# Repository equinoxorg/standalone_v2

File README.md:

#Standalone 2013 Designs

##Contents

* Hardware: The PCB designs for Pro and Home units
* Software: The source code of the embedded software
* Mechanical: The designs for the faceplate and physical casing
* Media: Any images or other media

##Hardware
This project includes hardware schematics and board layouts for Version 2 of the Standalone Battery Box (izuba.box) for e.quinox (www.e.quinox.org).

Cadsoft EAGLE v6 was the tool of choice when designing PCBs.

##Software

This project includes the ARM-based microcontroller software for Version 2 of the Standalone Battery Box (izuba.box) for e.quinox (www.e.quinox.org).

The project uses the Lite version of the Keil µVision IDE.

###Notes
Some code has been deliberately excluded as it would allow misuse of the payment system. If this is a problem please contact [info@e.quinox.org](mailto:info@e.quinox.org).

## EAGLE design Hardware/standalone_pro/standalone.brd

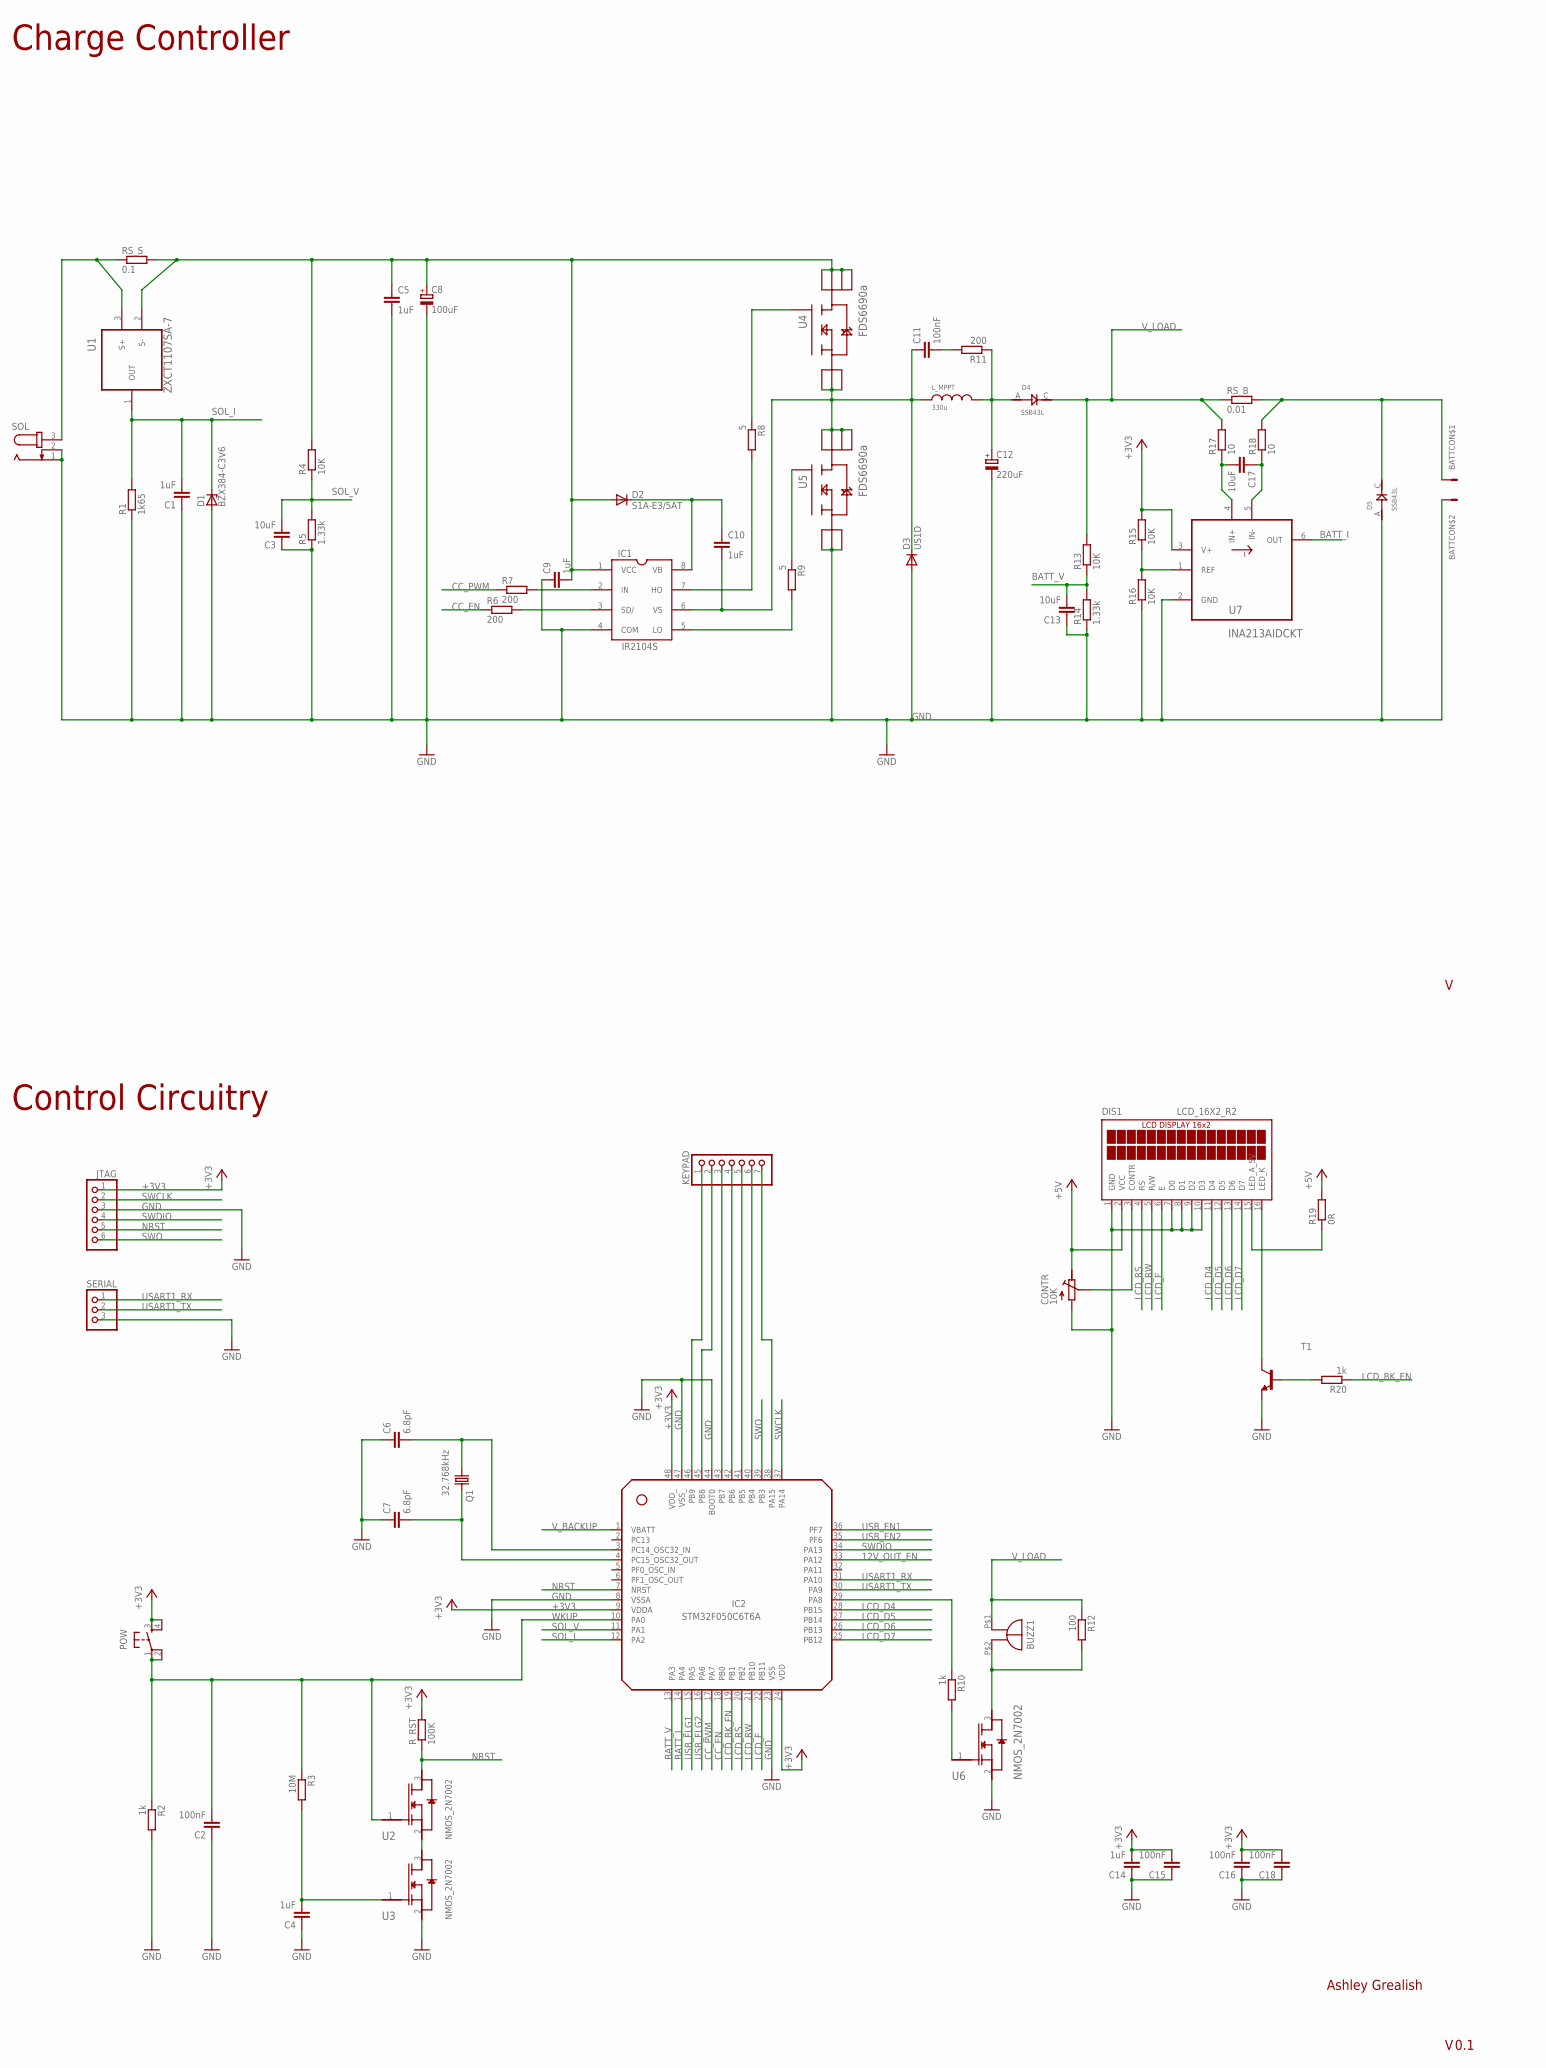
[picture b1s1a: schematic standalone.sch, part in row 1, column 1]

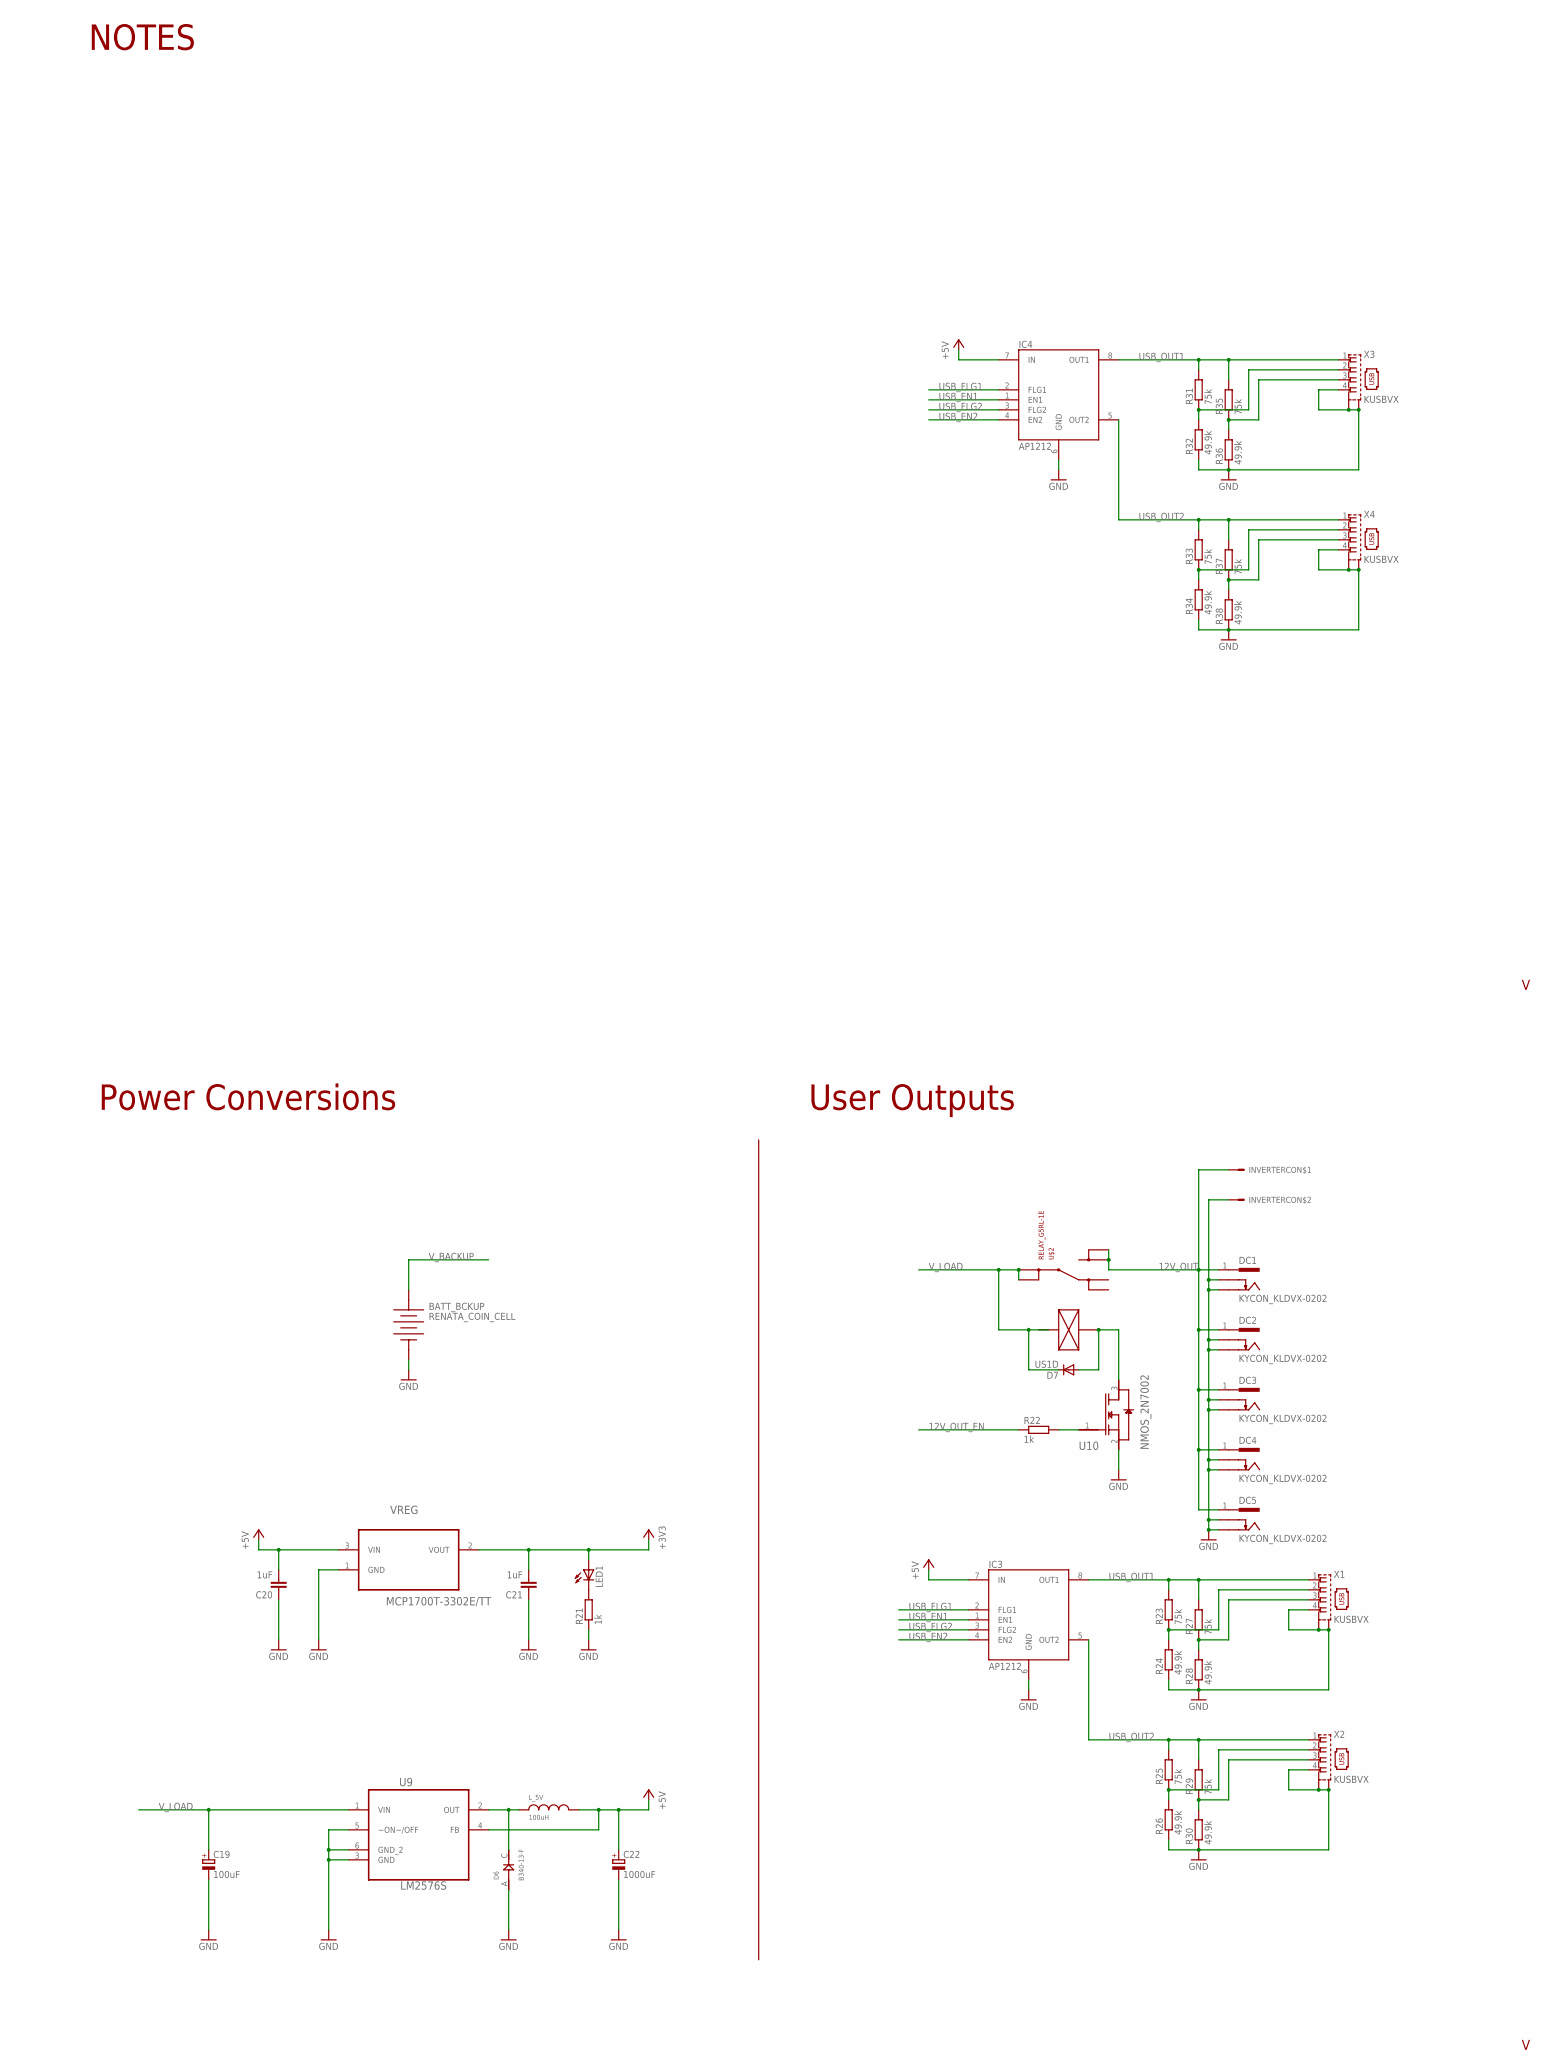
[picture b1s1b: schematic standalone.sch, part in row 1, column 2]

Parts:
BATT: CON_MOLEX_39_29_1028; MOLEX_39_29_1028
BATT_BCKUP: RENATA_COIN_CELL; PANASONIC_CR2032_1298246
BUZZ1: BUZZ_14MM; BUZZ_14MM_5M_PINS
C1, C4, C5, C9, C10, C14, C20, C21: 1uF; C0805K
C2, C11, C15, C16, C18: 100nF; C0805K
C3, C13, C17: 10uF; C0805K
C6, C7: 6.8pF; C0603K
C8, C19: 100uF; PANASONIC_E
C12: 220uF; PANASONIC_F
C22: 1000uF; PANASONIC_G
CONTR: 10K; R_TRIMM_RC33X
D1: BZX384-C3V6; SOD323
D2: S1A-E3/5AT; DO-214AC
D3, D7: US1D; DO-214AC
D4, D5: SSB43L; DO214AA
D6: B340-13-F; SMC
DC1, DC2, DC3, DC4, DC5: KYCON_KLDVX-0202; KYCON_KLVDX_2020_B
DIS1: LCD_16X2_R2
IC1: IR2104S
IC2: STM32F050C6T6A; LQFP48
IC3, IC4: AP1212; SO8
INVERTER: CON_MOLEX_39_29_1028; MOLEX_39_29_1028
JTAG: PINHD-1X6; 1X06
KEYPAD: PINHD-1X7/90; 1X07/90
LED1: POW_3V3; CHIPLED_0805
L_5V: 100uH; INDUC_BOURNS_SDR2207
L_MPPT: 330u; INDUC_MURATA_1433428C
POW: TAC_SWITCHPTH; TACTILE-PTH
Q1: 32.768kHz; MC-306; MPN MC-306
R1: 1k65; M0805
R2, R10, R20, R21, R22: 1k; M0805
R3: 10M; M0805
R4, R13, R15, R16: 10K; M0805
R5, R14: 1.33k; M0805
R6, R7, R11: 200; M0805
R8, R9: 5; M0805
R12: 100; M0805
R17, R18: 10; M0805
R19: 0R; M0805
R23, R25, R27, R29, R31, R33, R35, R37: 75k; M0805
R24, R26, R28, R30, R32, R34, R36, R38: 49.9k; M0805
RS_B: 0.01; R2512
RS_S: 0.1; R2512
R_RST: 100K; M0805
SERIAL: PINHD-1X3; 1X03
SOL: JACK-PLUG0; SPC4077
T1: BC847B-NPN-SOT23-BEC; SOT23-BEC
U1: ZXCT1107SA-7; SOT91P240X110-3N
U2, U3, U6: NMOS_2N7002; SOT103P240X110-3N; MPN 2N7002-7-F
U4, U5: FDS6690a; SOIC127P600X175-8N
U7: INA213AIDCKT; SOT65P210X110-6N
U9: LM2576S; TO263-5
U10: NMOS_2N7002; SOT103P240X110-3N
U$1: EQUINOX_LOGO_LARGE
U$2: RELAY_G5RL-1E; G5RL-1E
VREG: MCP1700T-3302E/TT; SOT95P237X112-3N
X1, X2, X3, X4: KUSBVX

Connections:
12V_OUT: DC1.1, DC2.1, DC3.1, DC4.1, DC5.1, INVERTER.P$1, U$2.NO@1 (NO), U$2.NO@2 (NO)
12V_OUT_EN: IC2.33 (PA12), R22.1
+3V3: C14.2, C15.2, C16.2, C18.2, C21.2, IC2.9 (VDDA), IC2.24 (VDD), IC2.48 (VDD_), JTAG.1, LED1.A, POW.3, POW.4, R15.2, R_RST.2, U7.3 (V+), VREG.2 (VOUT)
+5V: C20.2, C22.+, CONTR.CW (A), DIS1.2 (VCC), IC3.7 (IN), IC4.7 (IN), L_5V.P$2, R19.2, U9.4 (FB), VREG.3 (VIN)
BATT_I: IC2.14 (PA4), U7.6 (OUT)
BATT_V: C13.2, IC2.13 (PA3), R13.1, R14.2
CC_EN: IC2.18 (PB0), R6.1
CC_PWM: IC2.17 (PA7), R7.1
GND: BATT.P$2, BATT_BCKUP.P- (NEG), C1.1, C2.1, C3.1, C4.1, C5.2, C6.1, C7.1, C8.-, C9.1, C12.-, C13.1, C14.1, C15.1, C16.1, C18.1, C19.-, C20.1, C21.1, C22.-, CONTR.CCW (E), D1.A, D3.A, D5.A (ANODE), D6.A (ANODE), DC1.2, DC1.3, DC2.2, DC2.3, DC3.2, DC3.3, DC4.2, DC4.3, DC5.2, DC5.3, DIS1.1 (GND), DIS1.7 (D0), DIS1.8 (D1), DIS1.9 (D2), DIS1.10 (D3), IC1.4 (COM), IC2.8 (VSSA), IC2.23 (VSS), IC2.44 (BOOT0), IC2.47 (VSS_), IC3.6 (GND), IC4.6 (GND), INVERTER.P$2, JTAG.3, R1.1, R2.2, R5.1, R14.1, R16.1, R21.1, R24.1, R26.1, R28.1, R30.1, R32.1, R34.1, R36.1, R38.1, SERIAL.3, SOL.1, SOL.2, T1.E, U3.2 (S), U5.1 (S_2), U5.2 (S_3), U5.3 (S), U6.2 (S), U7.2 (GND), U9.3 (GND), U9.5 (~ON~/OFF), U9.6 (GND_2), U10.2 (S), VREG.1 (GND), X1.4, X1.M1 (S1), X1.M2 (S2), X2.4, X2.M1 (S1), X2.M2 (S2), X3.4, X3.M1 (S1), X3.M2 (S2), X4.4, X4.M1 (S1), X4.M2 (S2)
LCD_BK_EN: IC2.19 (PB1), R20.1
LCD_D4: DIS1.11 (D4), IC2.28 (PB15)
LCD_D5: DIS1.12 (D5), IC2.27 (PB14)
LCD_D6: DIS1.13 (D6), IC2.26 (PB13)
LCD_D7: DIS1.14 (D7), IC2.25 (PB12)
LCD_E: DIS1.6 (E), IC2.22 (PB11)
LCD_RS: DIS1.4 (RS), IC2.20 (PB2)
LCD_RW: DIS1.5 (R/W), IC2.21 (PB10)
unnamed: C6.2, IC2.3 (PC14_OSC32_IN), Q1.1
unnamed: CONTR.WIPE (S), DIS1.3 (CONTR)
unnamed: IC1.3 (SD/), R6.2
unnamed: BATT.P$1, D5.C (CATHODE), R18.2, RS_B.2
unnamed: R31.1, R32.2, X3.2
unnamed: C10.2, C11.1, D3.C, IC1.6 (VS), L_MPPT.P$1, U4.1 (S_2), U4.2 (S_3), U4.3 (S), U5.5 (D_3), U5.6 (D_2), U5.7 (D_4), U5.8 (D)
unnamed: IC1.7 (HO), R8.2
unnamed: IC1.2 (IN), R7.2
unnamed: C10.1, D2.C, IC1.8 (VB)
unnamed: R9.1, U5.4 (G)
unnamed: C12.+, D4.A (ANODE), L_MPPT.P$2, R11.1
unnamed: IC1.5 (LO), R9.2
unnamed: R8.1, U4.4 (G)
unnamed: C11.2, R11.2
unnamed: C5.1, C8.+, C9.2, D2.A, IC1.1 (VCC), R4.2, RS_S.2, U1.2 (S-), U4.5 (D_3), U4.6 (D_2), U4.7 (D_4), U4.8 (D)
unnamed: R35.1, R36.2, X3.3
unnamed: DIS1.15 (LED_A_5V), R19.1
unnamed: R25.1, R26.2, X2.2
unnamed: D6.C (CATHODE), L_5V.P$1, U9.2 (OUT)
unnamed: IC2.29 (PA8), R10.1
unnamed: IC2.46 (PB9), KEYPAD.1
unnamed: IC2.45 (PB8), KEYPAD.2
unnamed: IC2.43 (PB7), KEYPAD.3
unnamed: IC2.42 (PB6), KEYPAD.4
unnamed: IC2.41 (PB5), KEYPAD.5
unnamed: IC2.40 (PB4), KEYPAD.6
unnamed: IC2.38 (PA15), KEYPAD.7
unnamed: DIS1.16 (LED_K), T1.C
unnamed: R20.2, T1.B
unnamed: R23.1, R24.2, X1.2
unnamed: R27.1, R28.2, X1.3
unnamed: R22.2, U10.1 (G)
unnamed: R29.1, R30.2, X2.3
unnamed: LED1.C, R21.2
unnamed: RS_S.1, SOL.3, U1.3 (S+)
unnamed: R15.1, R16.2, U7.1 (REF)
unnamed: C17.2, R17.1, U7.4 (IN+)
unnamed: C17.1, R18.1, U7.5 (IN-)
unnamed: BUZZ1.P$2 (-), R12.2, U6.3 (D)
unnamed: R10.2, U6.1 (G)
unnamed: C4.2, R3.2, U3.1 (G)
unnamed: U2.2 (S), U3.3 (D)
unnamed: R33.1, R34.2, X4.2
unnamed: R37.1, R38.2, X4.3
unnamed: C7.2, IC2.4 (PC15_OSC32_OUT), Q1.4 (2)
unnamed: D7.A, U10.3 (D), U$2.COIL+
NRST: IC2.7 (NRST), JTAG.5, R_RST.1, U2.3 (D)
SOL_I: C1.2, D1.C, IC2.12 (PA2), R1.2, U1.1 (OUT)
SOL_V: C3.2, IC2.11 (PA1), R4.1, R5.2
SWCLK: IC2.37 (PA14), JTAG.2
SWDIO: IC2.34 (PA13), JTAG.4
SWO: IC2.39 (PB3), JTAG.6
USART1_RX: IC2.31 (PA10), SERIAL.1
USART1_TX: IC2.30 (PA9), SERIAL.2
USB_EN1: IC2.36 (PF7), IC3.1 (EN1), IC4.1 (EN1)
USB_EN2: IC2.35 (PF6), IC3.4 (EN2), IC4.4 (EN2)
USB_FLG1: IC2.15 (PA5), IC3.2 (FLG1), IC4.2 (FLG1)
USB_FLG2: IC2.16 (PA6), IC3.3 (FLG2), IC4.3 (FLG2)
USB_OUT1: IC3.8 (OUT1), IC4.8 (OUT1), R23.2, R27.2, R31.2, R35.2, X1.1, X3.1
USB_OUT2: IC3.5 (OUT2), IC4.5 (OUT2), R25.2, R29.2, R33.2, R37.2, X2.1, X4.1
V_BACKUP: BATT_BCKUP.P+ (POS), IC2.1 (VBATT)
V_LOAD: BUZZ1.P$1 (+), C19.+, D4.C (CATHODE), D7.C, R12.1, R13.2, R17.2, RS_B.1, U9.1 (VIN), U$2.COM@1 (COM), U$2.COM@2 (COM)
WKUP: C2.2, IC2.10 (PA0), POW.1, POW.2, R2.1, R3.1, U2.1 (G)

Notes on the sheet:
Charge Controller
Control Circuitry
Power Conversions
User Outputs
NOTES

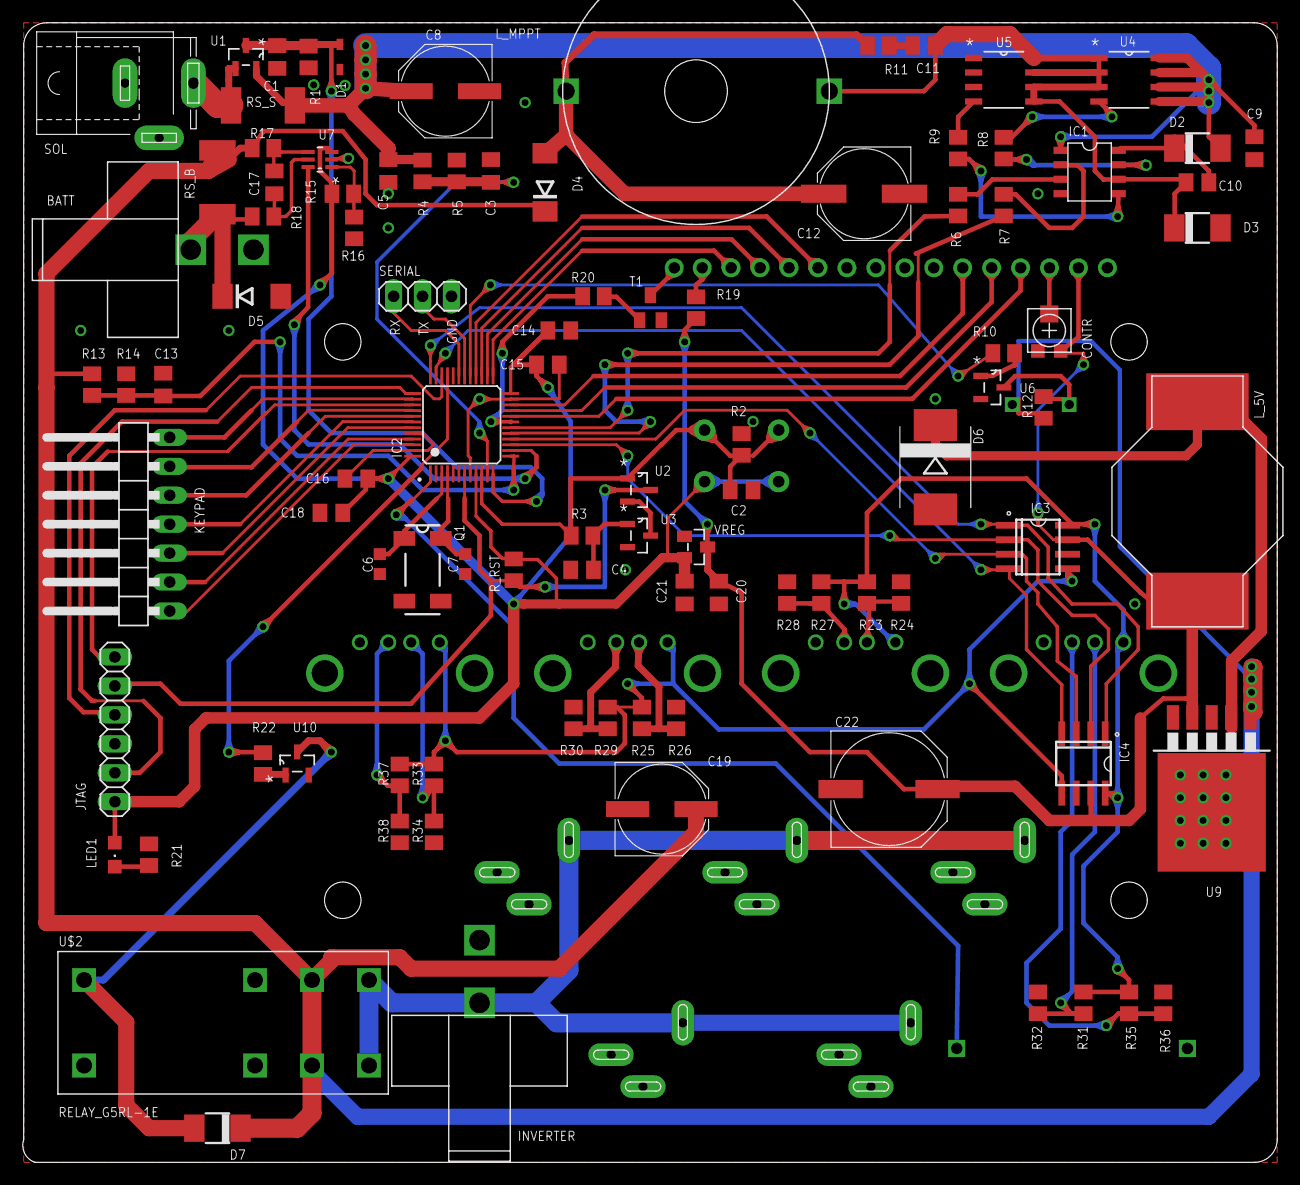
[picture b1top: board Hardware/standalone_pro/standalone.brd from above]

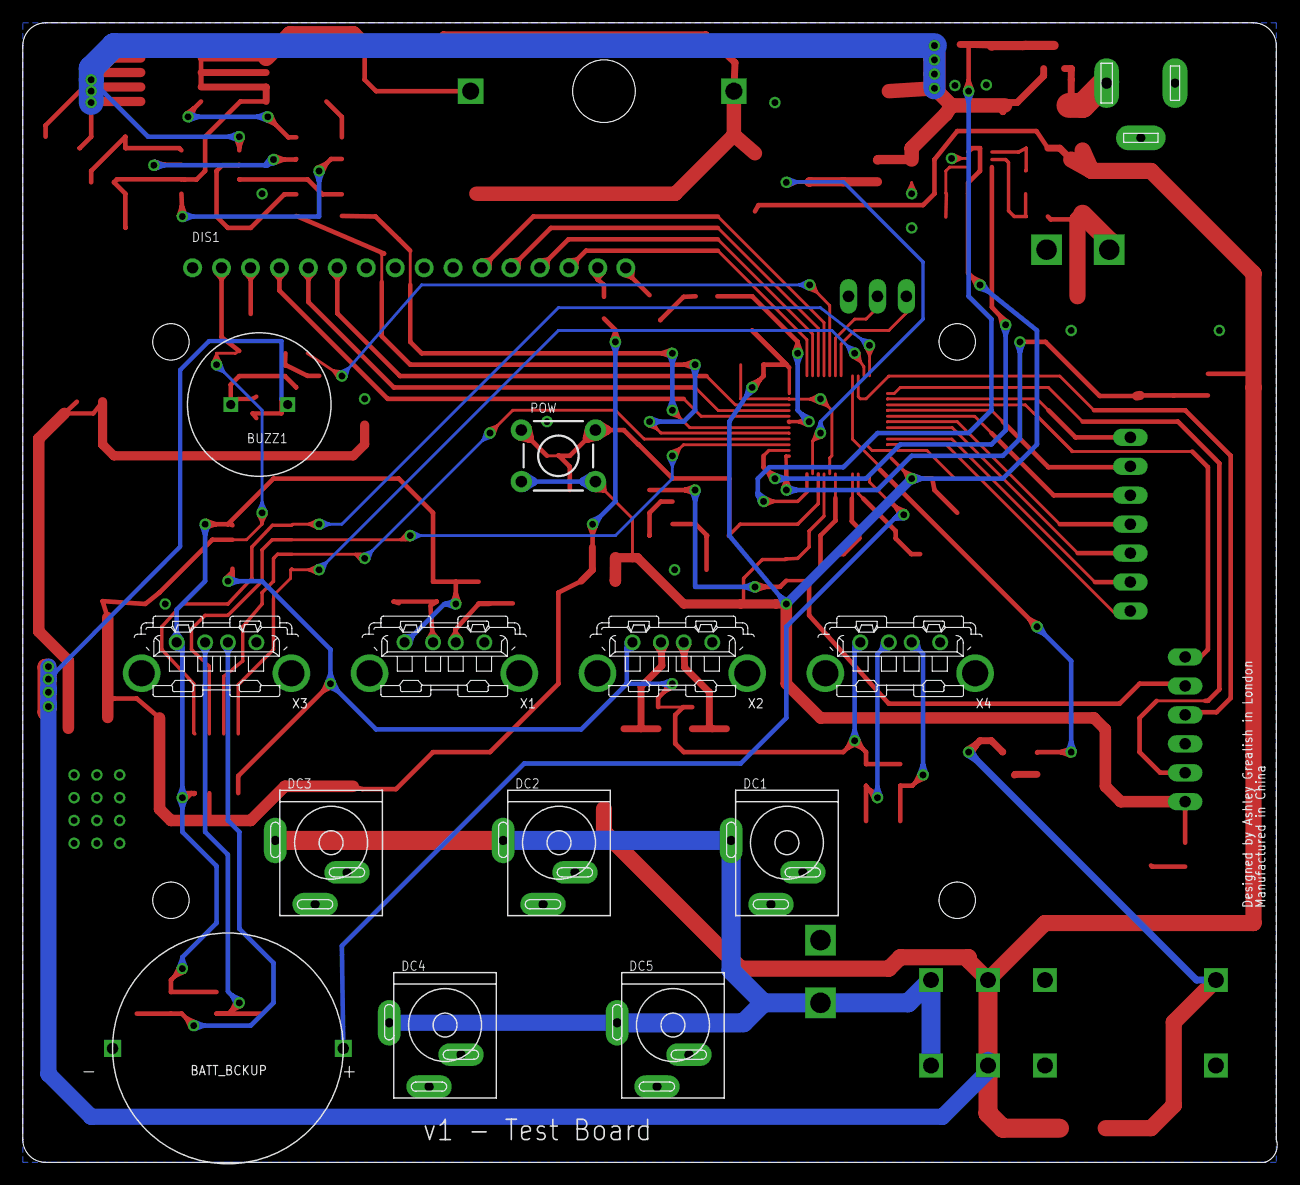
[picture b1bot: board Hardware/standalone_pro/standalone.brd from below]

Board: 2 copper layers, 110.1 x 100.0 mm, 111 parts (14 on the bottom side), 80 nets.

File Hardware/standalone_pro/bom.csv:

"Qty";"Value";"Device";"Package";"Parts";"Description";"FARNELL";"MF";"MPN";"OC_FARNELL";"OC_MOUSER";"OC_NEWARK";"PACKAGE";"RS";"SUPPLIER";"TOBY";
"1";"";"BC847B-NPN-SOT23-BEC";"SOT23-BEC";"T1";"NPN Transistror";"";"";"";"";"";"";"";"";"";"";
"1";"";"JACK-PLUG0";"SPC4077";"SOL";"DC POWER JACK";"";"";"";"unknown";"";"unknown";"";"";"";"DC-001-A-2.1mm-R";
"1";"";"PINHD-1X3";"1X03";"SERIAL";"PIN HEADER";"";"";"";"";"";"";"";"";"";"";
"1";"";"PINHD-1X6";"1X06";"JTAG";"PIN HEADER";"";"";"";"";"";"";"";"";"";"";
"1";"";"PINHD-1X7/90";"1X07/90";"KEYPAD";"PIN HEADER";"";"";"";"588763";"";"";"";"";"";"";
"1";"";"TAC_SWITCHPTH";"TACTILE-PTH";"POW";"Momentary Switch";"";"";"";"";"";"";"";"758-1979";"";"";
"1";"0.01";"R-EU_R2512";"R2512";"RS_B";"RESISTOR, European symbol";"";"";"";"";"";"";"";"";"";"";
"1";"0.1";"R-EU_R2512";"R2512";"RS_S";"RESISTOR, European symbol";"";"";"";"";"";"";"";"";"";"";
"1";"0R";"R-EU_M0805";"M0805";"R19";"RESISTOR, European symbol";"";"";"";"";"";"";"";"";"";"";
"2";"1.33k";"R-EU_M0805";"M0805";"R5, R14";"RESISTOR, European symbol";"";"";"";"";"";"";"";"";"";"";
"2";"10";"R-EU_M0805";"M0805";"R17, R18";"RESISTOR, European symbol";"";"";"";"";"";"";"";"";"";"";
"1";"100";"R-EU_M0805";"M0805";"R12";"RESISTOR, European symbol";"";"";"";"";"";"";"";"";"";"";
"1";"1000uF";"CPOL-EUG";"PANASONIC_G";"C22";"POLARIZED CAPACITOR, European symbol";"";"";"";"1244342";"";"";"";"";"";"";
"1";"100K";"R-EU_M0805";"M0805";"R_RST";"RESISTOR, European symbol";"";"";"";"";"";"";"";"";"";"";
"5";"100nF";"C-EUC0805K";"C0805K";"C2, C11, C15, C16, C18";"CAPACITOR, European symbol";"";"";"";"";"";"";"";"";"";"";
"2";"100uF";"CPOL-EUE";"PANASONIC_E";"C8, C19";"POLARIZED CAPACITOR, European symbol";"";"";"";"1539489";"";"";"";"";"";"";
"1";"100uH";"INDUC_BOURNES_SDR2207";"INDUC_BOURNS_SDR2207";"L_5V";"";"1612709";"";"";"1612709";"";"";"";"";"";"";
"4";"10K";"R-EU_M0805";"M0805";"R4, R13, R15, R16";"RESISTOR, European symbol";"";"";"";"";"";"";"";"";"";"";
"1";"10K";"R_TRIMM_TC33X";"R_TRIMM_RC33X";"CONTR";"";"";"";"";"1689863";"652-TC33X-2-103E";"";"";"";"";"";
"1";"10M";"R-EU_M0805";"M0805";"R3";"RESISTOR, European symbol";"";"";"";"";"";"";"";"";"";"";
"3";"10uF";"C-EUC0805K";"C0805K";"C3, C13, C17";"CAPACITOR, European symbol";"";"";"";"";"";"";"";"";"";"";
"5";"1k";"R-EU_M0805";"M0805";"R2, R10, R20, R21, R22";"RESISTOR, European symbol";"";"";"";"";"";"";"";"";"";"";
"1";"1k65";"R-EU_M0805";"M0805";"R1";"RESISTOR, European symbol";"";"";"";"";"";"";"";"";"";"";
"8";"1uF";"C-EUC0805K";"C0805K";"C1, C4, C5, C9, C10, C14, C20, C21";"CAPACITOR, European symbol";"";"";"";"";"";"";"";"";"";"";
"3";"200";"R-EU_M0805";"M0805";"R6, R7, R11";"RESISTOR, European symbol";"";"";"";"";"";"";"";"";"";"";
"1";"220uF";"CPOL-EUF";"PANASONIC_F";"C12";"POLARIZED CAPACITOR, European symbol";"";"";"";"9695877";"";"";"";"";"";"";
"1";"32.768kHz";"MC-306";"MC-306";"Q1";"kHz RANGE CRYSTAL UNIT SMD";"";"";"MC-306";"1712823";"";"-";"";"";"";"";
"1";"330u";"INDUC_MURATA_1433428C";"INDUC_MURATA_1433428C";"L_MPPT";"";"";"";"";"1077018";"";"";"";"";"";"";
"8";"49.9k";"R-EU_M0805";"M0805";"R24, R26, R28, R30, R32, R34, R36, R38";"RESISTOR, European symbol";"";"";"";"";"";"";"";"";"";"";
"2";"5";"R-EU_M0805";"M0805";"R8, R9";"RESISTOR, European symbol";"";"";"";"";"";"";"";"";"";"";
"2";"6.8pF";"C-EUC0603K";"C0603K";"C6, C7";"CAPACITOR, European symbol";"";"";"";"1856141";"";"";"";"";"";"";
"8";"75k";"R-EU_M0805";"M0805";"R23, R25, R27, R29, R31, R33, R35, R37";"RESISTOR, European symbol";"";"";"";"";"";"";"";"";"";"";
"2";"AP1212";"AP1212";"SO8";"IC3, IC4";"Datasheet: http://www.farnell.com/datasheets/608767.pdf";"";"";"";"1825302";"";"";"";"";"";"";
"1";"B340-13-F";"DIODE_B340-13-F";"SMC";"D6";"";"";"";"";"1843695";"";"";"";"";"";"";
"1";"BUZZ_14MM";"BUZZ_14MM";"BUZZ_14MM_5M_PINS";"BUZZ1";"";"";"";"";"1192513";"";"";"";"";"";"";
"1";"BZX384-C3V6";"BZX384-C3V6";"SOD323";"D1";"";"";"";"";"8735654";"";"";"";"";"";"";
"2";"CON_MOLEX_39_29_1028";"CON_MOLEX_39_29_1028";"MOLEX_39_29_1028";"BATT, INVERTER";"";"";"";"";"1012166";"";"";"";"";"";"";
"1";"EQUINOX_LOGO_LARGE";"EQUINOX_LOGO_LARGE";"EQUINOX_LOGO_LARGE";"U$1";"";"";"";"";"";"";"";"";"";"";"";
"2";"FDS6690a";"DMS3016SSS-13";"SOIC127P600X175-8N";"U4, U5";"ENHANCEMENT MODE MOSFET";"";"";"";"9845275";"";"";"SOIC-8";"";"";"";
"1";"INA213AIDCKT";"INA213AIDCKT";"SOT65P210X110-6N";"U7";"CURRENT SHUNT MONITOR";"";"";"INA213AIDCKT";"1754261";"";"05N1040";"SC-70-6";"";"Texas Instruments";"";
"1";"IR2104S";"IR2104S";"IR2104S";"IC1";"Half Bridge Mosfet - IGBT driver SOIC";"";"";"";"8638756";"";"";"";"";"";"";
"4";"KUSBVX";"KUSBVX";"KUSBVX";"X1, X2, X3, X4";"Vertical,Top Entry Universal Serial Bus Connector KUSBVX Series";"";"";"";"";"";"";"";"";"";"";
"5";"KYCON_KLDVX-0202";"KYCON_KLDVX-0202";"KYCON_KLVDX_2020_B";"DC1, DC2, DC3, DC4, DC5";"";"";"";"";"";"";"";"";"";"";"DC-031-B";
"1";"LCD_16X2_R2";"LCD_16X2_R2";"LCD_16X2_R2";"DIS1";"Supplier: info";"";"";"";"unknown";"";"unknown";"";"";"";"";
"1";"LM2576S";"LM2576S";"TO263-5";"U9";"";"";"";"";"1469178";"";"";"";"";"";"";
"1";"MCP1700T-3302E/TT";"MCP1700T-3302E/TT";"SOT95P237X112-3N";"VREG";"Low Quiescent Current LDO";"";"";"MCP1700T-3302E/TT";"1296592";"";"88H9817";"SOT23-3";"";"Microchip";"";
"4";"NMOS_2N7002";"NMOS_2N7002";"SOT103P240X110-3N";"U2, U3, U6, U10";"N-CHANNEL ENHANCEMENT MODE FIELD EFFECT TRANSISTOR";"";"";"2N7002-7-F";"1713823";"";"25R5679";"SOT-23-3";"";"DIODES INC.";"";
"1";"POW_3V3";"LEDCHIPLED_0805";"CHIPLED_0805";"LED1";"LED";"";"";"";"";"";"";"";"";"";"";
"1";"RELAY_G5RL-1E";"RELAY_G5RL-1E";"G5RL-1E";"U$2";"";"";"";"";"";"";"";"";"";"";"";
"1";"RENATA_COIN_CELL";"PANASONIC_CR2032_1298246";"PANASONIC_CR2032_1298246";"BATT_BCKUP";"Farnell Part No: 1298246";"";"";"";"1298246 ";"";"";"";"";"";"";
"1";"S1A-E3/5AT";"DIODE-DO-214AC";"DO-214AC";"D2";"DIODE";"";"";"";"9550216";"";"";"";"";"";"";
"2";"SSB43L";"DIODE_SSB43L";"DO214AA";"D4, D5";"VISHAY - SSB43L-E3/52T - DIODE, SCHOTTKY, 4A, 30V";"";"";"";"1336556";"";"";"";"";"";"";
"1";"STM32F050C6T6A";"STM32F050C6T6A";"LQFP48";"IC2";"";"";"";"";"2115059";"";"";"";"";"";"";
"2";"US1D";"DIODE-DO-214AC";"DO-214AC";"D3, D7";"DIODE";"";"";"";"1625280";"";"";"";"";"";"";
"1";"ZXCT1107SA-7";"ZXCT1107SA-7";"SOT91P240X110-3N";"U1";"LOW POWER HIGH-SIDE CURRENT MONITORS";"";"";"ZXCT1107SA-7";"1904027";"";"55T4047";"SOT-23-3";"";"DIODES INC.";"";

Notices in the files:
parts and their libraries:
SparkFun: Licensing: CC v3.0 Share-Alike You are welcome to use this library for commercial purposes.
